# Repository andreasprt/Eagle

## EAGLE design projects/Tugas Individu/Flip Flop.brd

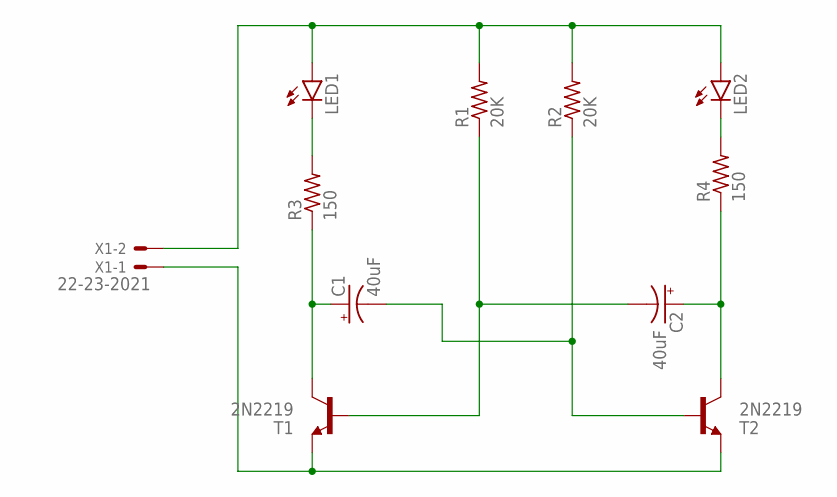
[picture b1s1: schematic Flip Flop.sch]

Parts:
C1, C2: 40uF; E2,5-6
LED1, LED2: LED5MM
R1, R2: 20K; 0207/10
R3, R4: 150; 0207/10
T1, T2: 2N2219; TO5
X1: 22-23-2021

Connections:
GND: T1.1 (E), T2.1 (E), X1.1
unnamed: LED1.K (C), R3.2
unnamed: LED2.K (C), R4.2
unnamed: C1.+, R3.1, T1.3 (C)
unnamed: C2.+, R4.1, T2.3 (C)
unnamed: C2.-, R1.1, T1.2 (B)
unnamed: C1.-, R2.1, T2.2 (B)
unnamed: LED1.A, LED2.A, R1.2, R2.2, X1.2

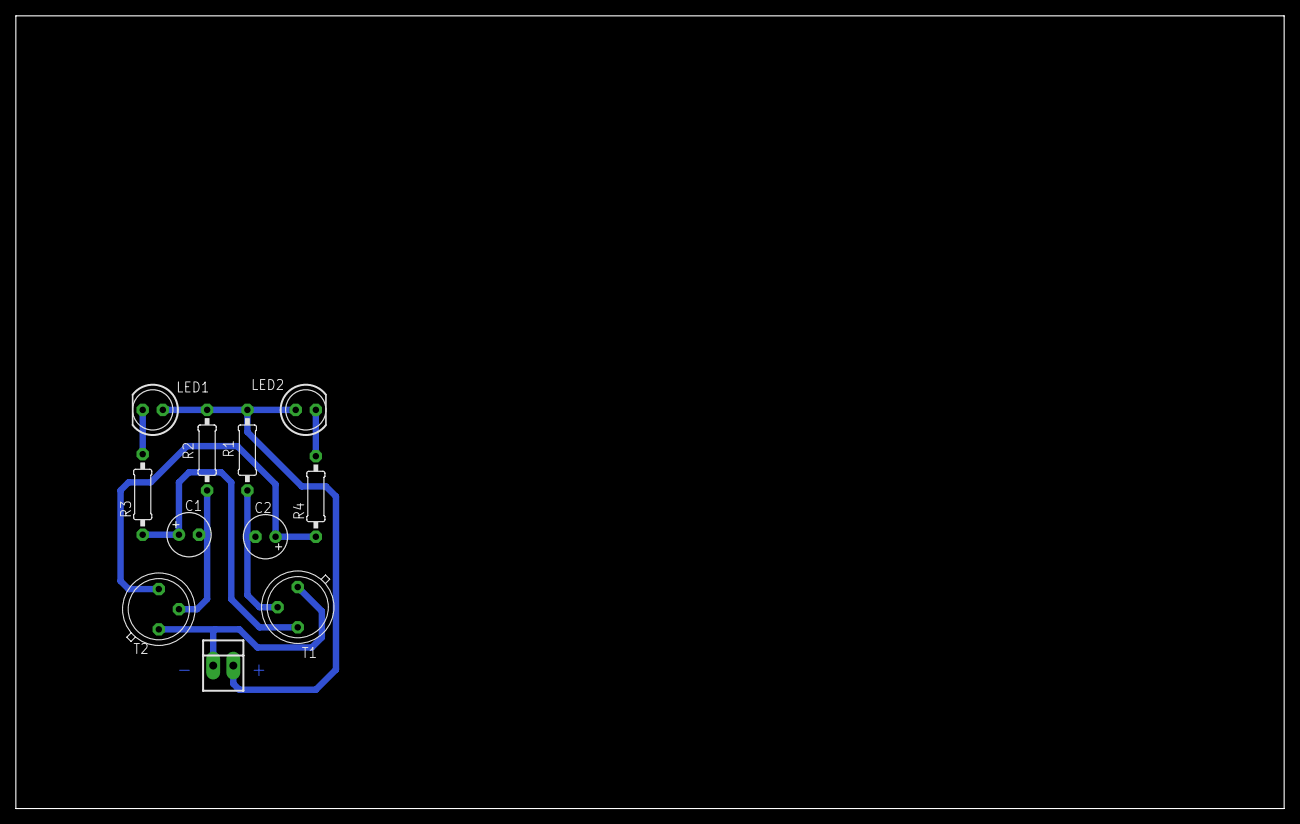
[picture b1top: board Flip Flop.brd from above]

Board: 2 copper layers, 160.0 x 100.0 mm, 11 parts (0 on the bottom side), 8 nets.

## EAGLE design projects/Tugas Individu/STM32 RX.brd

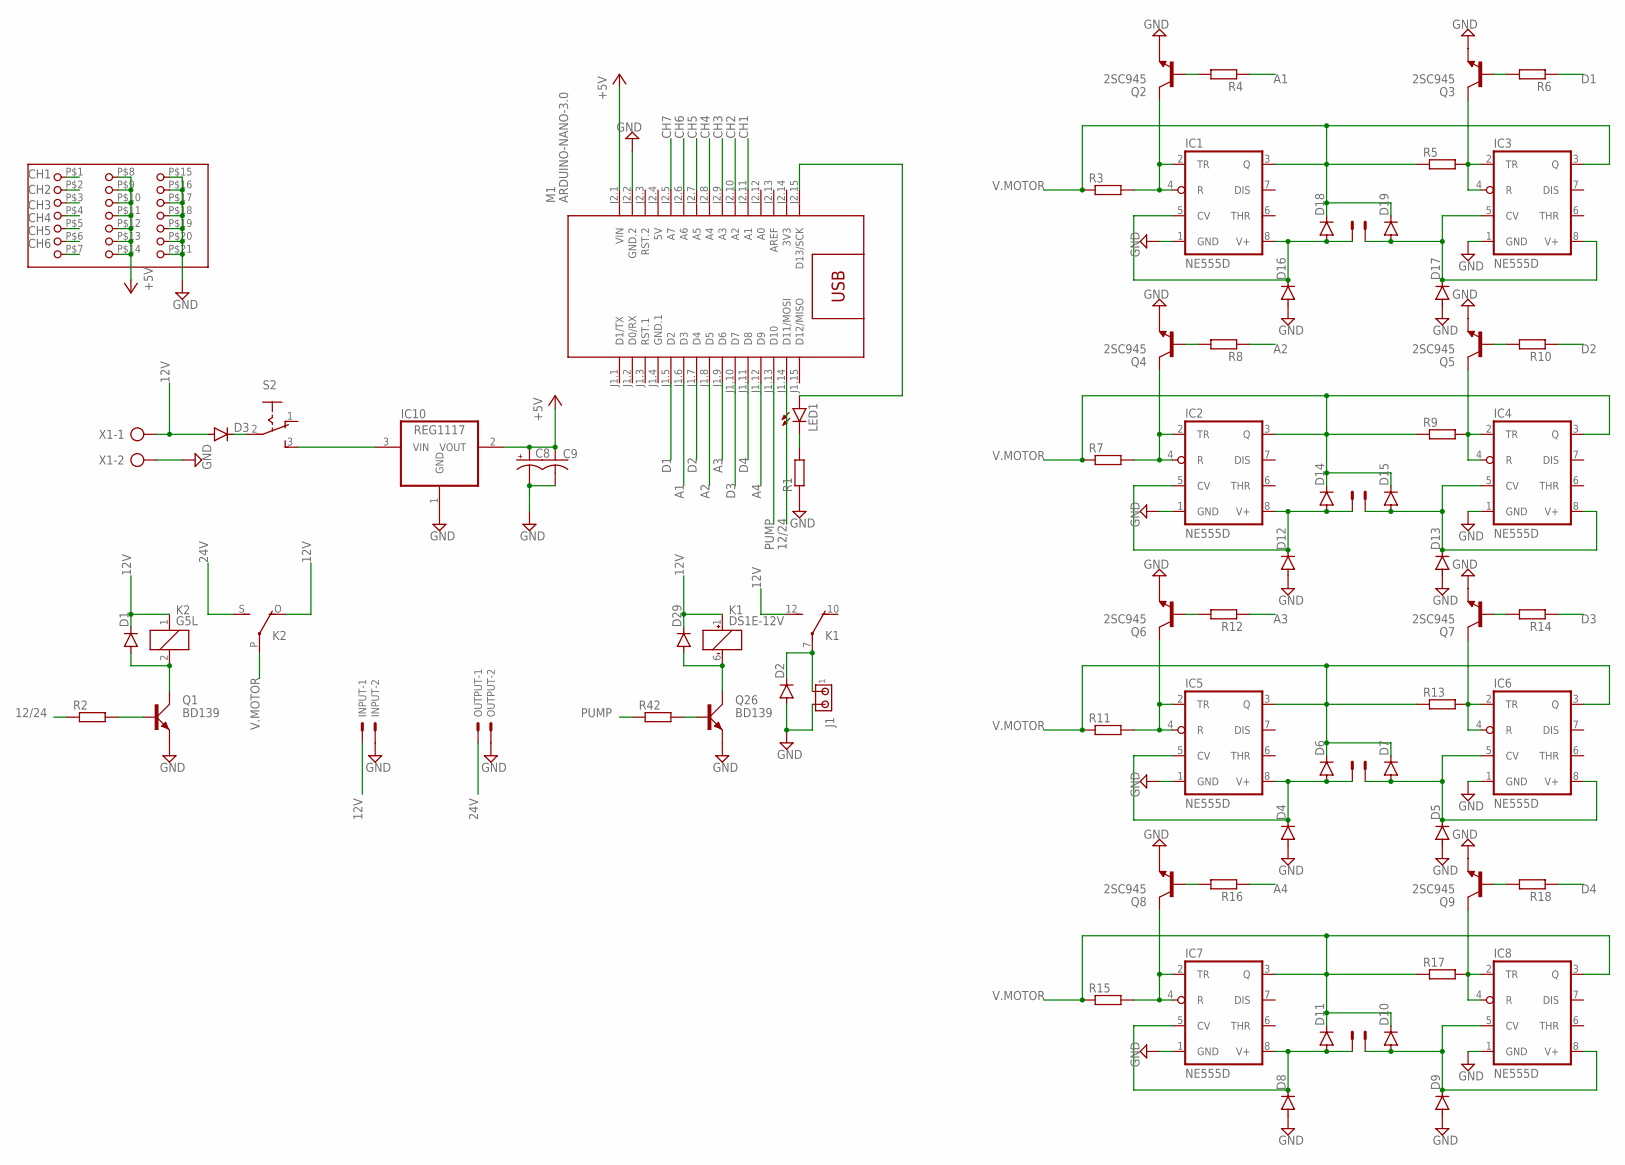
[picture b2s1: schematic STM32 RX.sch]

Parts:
C8: CPOL-USE2.5-6; E2,5-6
C9: C-US050-025X075; C050-025X075
D1, D2, D3, D4, D5, D6, D7, D8, D9, D10, D11, D12, D13, D14, D15, D16, D17, D18, D19, D29: 1N4933; DO41-10
IC1, IC2, IC3, IC4, IC5, IC6, IC7, IC8: NE555D; SO08
IC10: REG1117; SOT223
INPUT: 22-23-2021
J1: MTA02-156; 1X2MTA
K1: DS1E-12V; DS1E
K2: G5L; G5LE
LED1: LED5MM
M1: ARDUINO-NANO-3.0
OUTPUT, OUTPUT1, OUTPUT2, OUTPUT3, OUTPUT4: 22-23-2021
Q1, Q26: BD139; TO126AV
Q2, Q3, Q4, Q5, Q6, Q7, Q8, Q9: 2SC945; TO92-ECB
R1, R2, R3, R4, R5, R6, R7, R8, R9, R10, R11, R12, R13, R14, R15, R16, R17, R18, R42: R-EU_0207/10; 0207/10
S2: 255SB
U$1: PINHEAD3
X1: AK500/2

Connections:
3V3: M1.J2.14 (3V3)
5V: M1.J2.4 (5V)
12/24: M1.J1.14 (D11/MOSI), R2.1
12V: D1.C, D3.A, D29.C, INPUT.1, K1.1 (+), K1.12 (S), K2.1, K2.O, X1.1
24V: K2.S, OUTPUT.1
+5V: C8.+, C9.1, IC10.2 (VOUT), M1.J2.1 (VIN), U$1.P$8, U$1.P$9, U$1.P$10, U$1.P$11, U$1.P$12, U$1.P$13, U$1.P$14
A1: M1.J1.6 (D3), R4.1
A2: M1.J1.8 (D5), R8.1
A3: M1.J1.9 (D6), R12.1
A4: M1.J1.12 (D9), R16.1
CH1: M1.J2.11 (A1), U$1.P$1
CH2: M1.J2.10 (A2), U$1.P$2
CH3: M1.J2.9 (A3), U$1.P$3
CH4: M1.J2.8 (A4), U$1.P$4
CH5: M1.J2.7 (A5), U$1.P$5
CH6: M1.J2.6 (A6), U$1.P$6
CH7: M1.J2.5 (A7)
D1: M1.J1.5 (D2), R6.1
D2: M1.J1.7 (D4), R10.1
D3: M1.J1.10 (D7), R14.1
D4: M1.J1.11 (D8), R18.1
GND: C8.-, C9.2, D2.A, D4.A, D5.A, D8.A, D9.A, D12.A, D13.A, D16.A, D17.A, IC1.1 (GND), IC2.1 (GND), IC3.1 (GND), IC4.1 (GND), IC5.1 (GND), IC6.1 (GND), IC7.1 (GND), IC8.1 (GND), IC10.1 (GND), INPUT.2, J1.2, M1.J2.2 (GND.2), OUTPUT.2, Q1.E, Q2.E, Q3.E, Q4.E, Q5.E, Q6.E, Q7.E, Q8.E, Q9.E, Q26.E, R1.1, U$1.P$15, U$1.P$16, U$1.P$17, U$1.P$18, U$1.P$19, U$1.P$20, U$1.P$21, X1.2
GND.1: M1.J1.4 (GND.1)
unnamed: LED1.A, M1.J2.15 (D13/SCK)
unnamed: D1.A, K2.2, Q1.C
unnamed: LED1.K (C), R1.2
unnamed: Q1.B, R2.2
unnamed: D3.C, S2.2
unnamed: IC10.3 (VIN), S2.3 (S)
unnamed: IC1.2 (TR), IC1.4 (R), Q2.C, R3.2
unnamed: D16.C, D18.A, IC1.5 (CV), IC1.8 (V+), OUTPUT1.1
unnamed: IC2.2 (TR), IC2.4 (R), Q4.C, R7.2
unnamed: Q2.B, R4.2
unnamed: IC3.2 (TR), IC3.4 (R), Q3.C, R5.2
unnamed: D17.C, D19.A, IC3.5 (CV), IC3.8 (V+), OUTPUT1.2
unnamed: Q3.B, R6.2
unnamed: D12.C, D14.A, IC2.5 (CV), IC2.8 (V+), OUTPUT2.1
unnamed: Q4.B, R8.2
unnamed: IC4.2 (TR), IC4.4 (R), Q5.C, R9.2
unnamed: D13.C, D15.A, IC4.5 (CV), IC4.8 (V+), OUTPUT2.2
unnamed: Q5.B, R10.2
unnamed: IC5.2 (TR), IC5.4 (R), Q6.C, R11.2
unnamed: D4.C, D6.A, IC5.5 (CV), IC5.8 (V+), OUTPUT3.1
unnamed: Q6.B, R12.2
unnamed: IC6.2 (TR), IC6.4 (R), Q7.C, R13.2
unnamed: D5.C, D7.A, IC6.5 (CV), IC6.8 (V+), OUTPUT3.2
unnamed: Q7.B, R14.2
unnamed: IC7.2 (TR), IC7.4 (R), Q8.C, R15.2
unnamed: D8.C, D11.A, IC7.5 (CV), IC7.8 (V+), OUTPUT4.1
unnamed: Q8.B, R16.2
unnamed: IC8.2 (TR), IC8.4 (R), Q9.C, R17.2
unnamed: D9.C, D10.A, IC8.5 (CV), IC8.8 (V+), OUTPUT4.2
unnamed: Q9.B, R18.2
unnamed: D2.C, J1.1, K1.7
unnamed: D29.A, K1.6 (-), Q26.C
unnamed: Q26.B, R42.2
PUMP: M1.J1.13 (D10), R42.1
V.MOTOR: D6.C, D7.C, D10.C, D11.C, D14.C, D15.C, D18.C, D19.C, IC1.3 (Q), IC2.3 (Q), IC3.3 (Q), IC4.3 (Q), IC5.3 (Q), IC6.3 (Q), IC7.3 (Q), IC8.3 (Q), K2.P, R3.1, R5.1, R7.1, R9.1, R11.1, R13.1, R15.1, R17.1

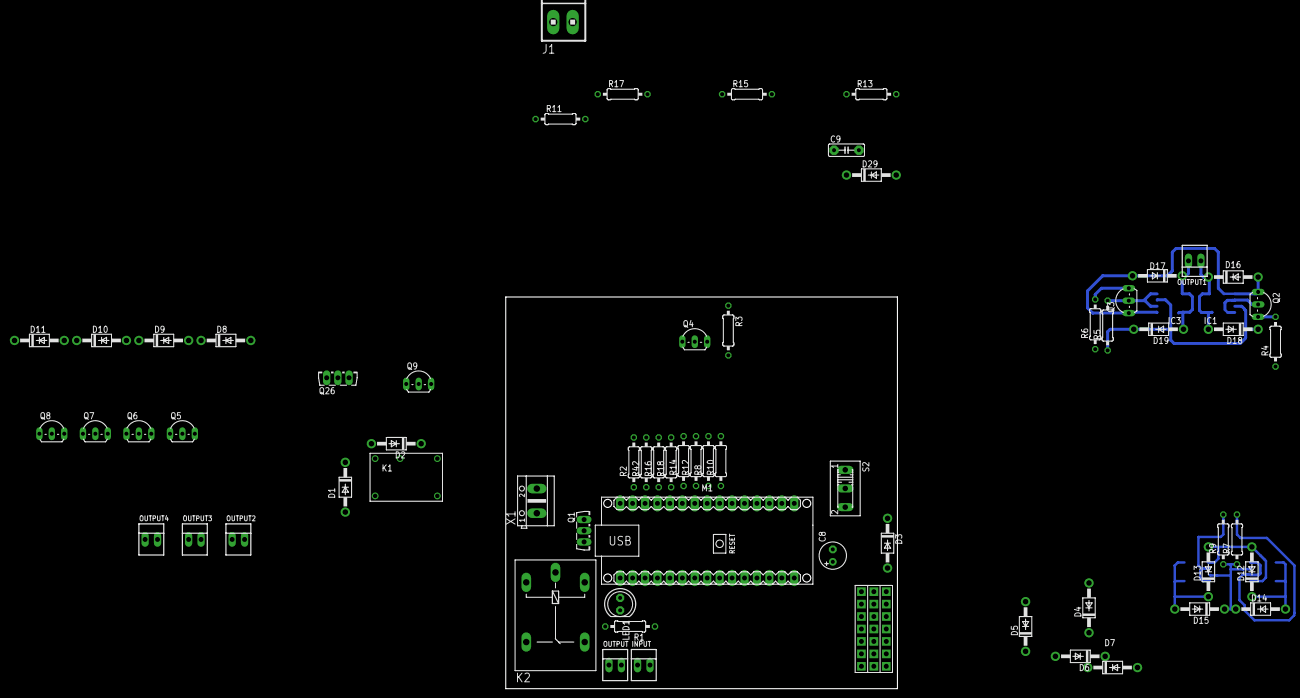
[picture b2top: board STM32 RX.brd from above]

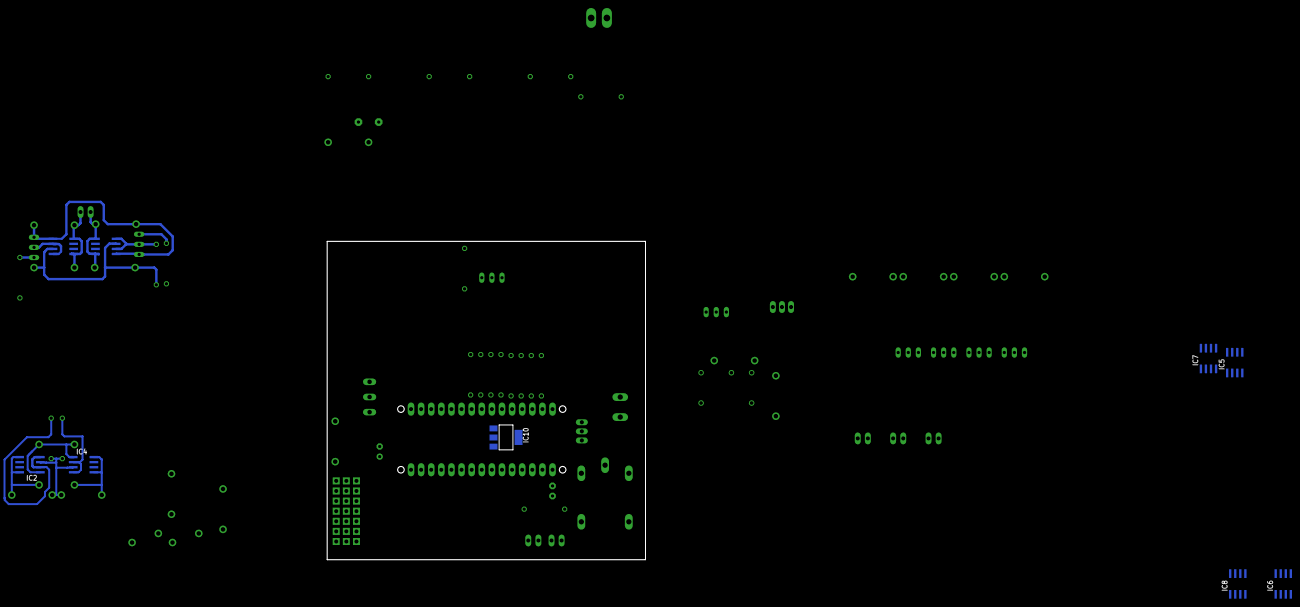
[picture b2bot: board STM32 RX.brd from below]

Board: 2 copper layers, 80.0 x 80.0 mm, 74 parts (9 on the bottom side), 54 nets.

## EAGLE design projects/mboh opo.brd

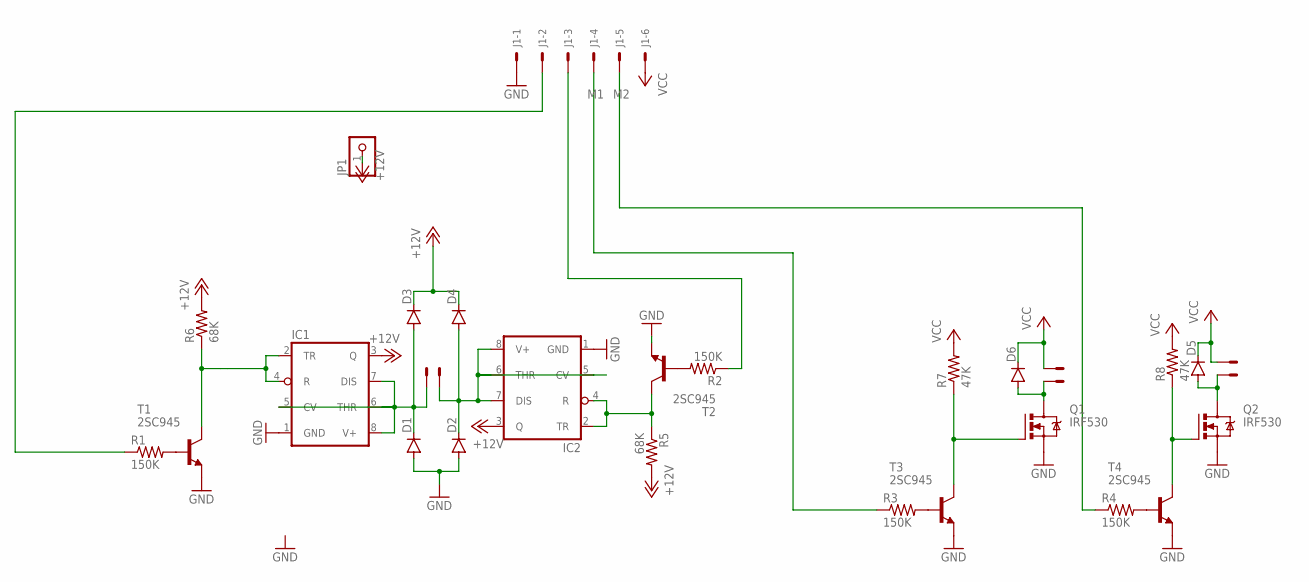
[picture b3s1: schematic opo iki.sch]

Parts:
D1, D2, D3, D4, D5, D6: 1N4004; DO41-10
IC1, IC2: LM555D; SO08
J1: 22-27-2061-06; 6410-06
JP1: PINHD-1X1; 1X01
Q1, Q2: IRF530; TO220BV
R1, R2, R3, R4: 150K; 0309/10
R5, R6: 68K; 0309/10
R7, R8: 47K; 0309/10
T1, T2, T3, T4: 2SC945; TO92-ECB
X1, X2, X3: 22-23-2021

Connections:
+12V: D3.C, D4.C, IC1.3 (Q), IC2.3 (Q), JP1.1, R5.2, R6.2
GND: D1.A, D2.A, IC1.1 (GND), IC2.1 (GND), J1.1, Q1.S, Q2.S, T1.E, T2.E, T3.E, T4.E
M1: J1.4, R3.1
M2: J1.5, R4.1
unnamed: R1.2, T1.B
unnamed: R2.2, T2.B
unnamed: IC2.2 (TR), IC2.4 (R), R5.1, T2.C
unnamed: IC1.2 (TR), IC1.4 (R), R6.1, T1.C
unnamed: R3.2, T3.B
unnamed: D1.C, D3.A, IC1.5 (CV), IC1.6 (THR), IC1.7 (DIS), IC1.8 (V+), X3.1
unnamed: D2.C, D4.A, IC2.5 (CV), IC2.6 (THR), IC2.7 (DIS), IC2.8 (V+), X3.2
unnamed: R4.2, T4.B
unnamed: Q1.G, R7.1, T3.C
unnamed: Q2.G, R8.1, T4.C
unnamed: D6.A, Q1.D, X1.2
unnamed: D5.A, Q2.D, X2.2
unnamed: J1.2, R1.1
unnamed: J1.3, R2.1
VCC: D5.C, D6.C, J1.6, R7.2, R8.2, X1.1, X2.1

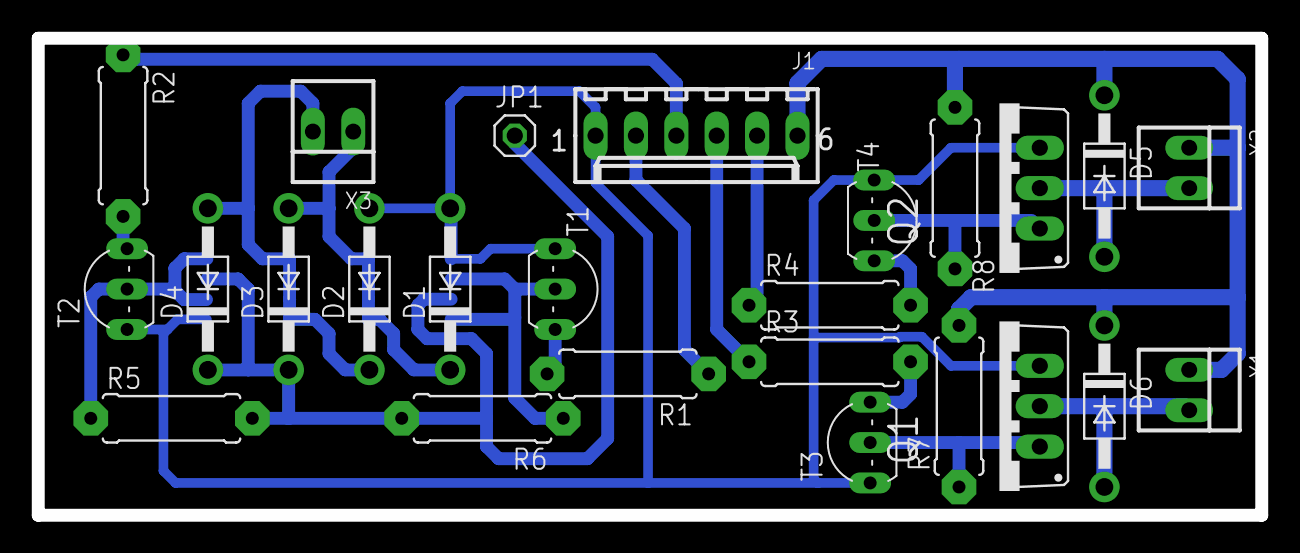
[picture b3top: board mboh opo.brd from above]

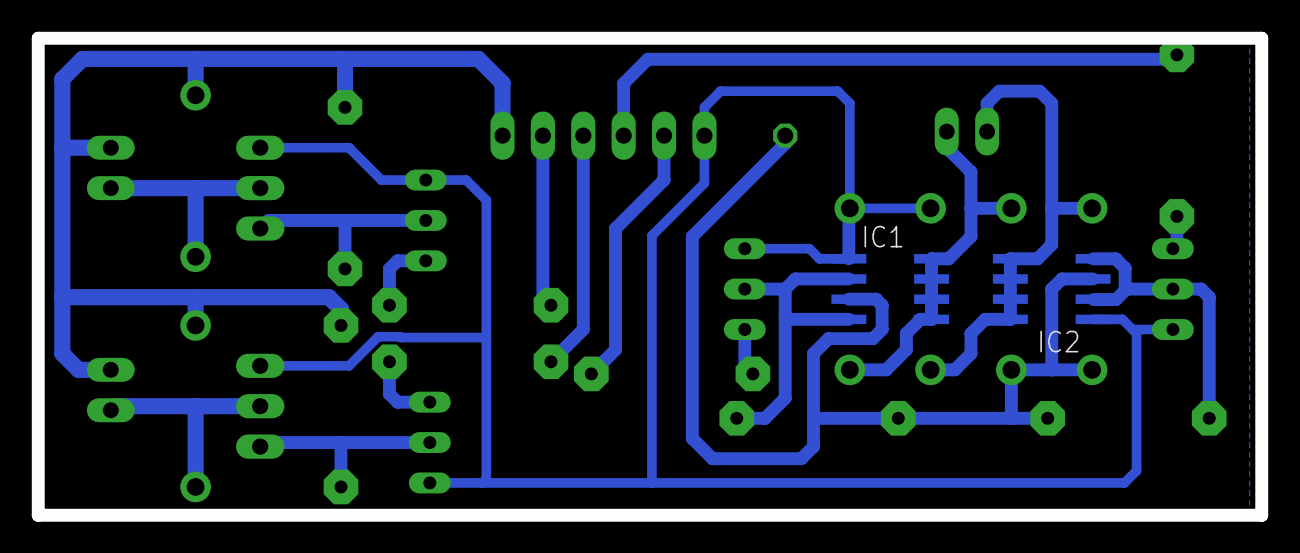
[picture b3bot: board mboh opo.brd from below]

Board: 2 copper layers, 77.0 x 30.0 mm, 27 parts (2 on the bottom side), 19 nets.

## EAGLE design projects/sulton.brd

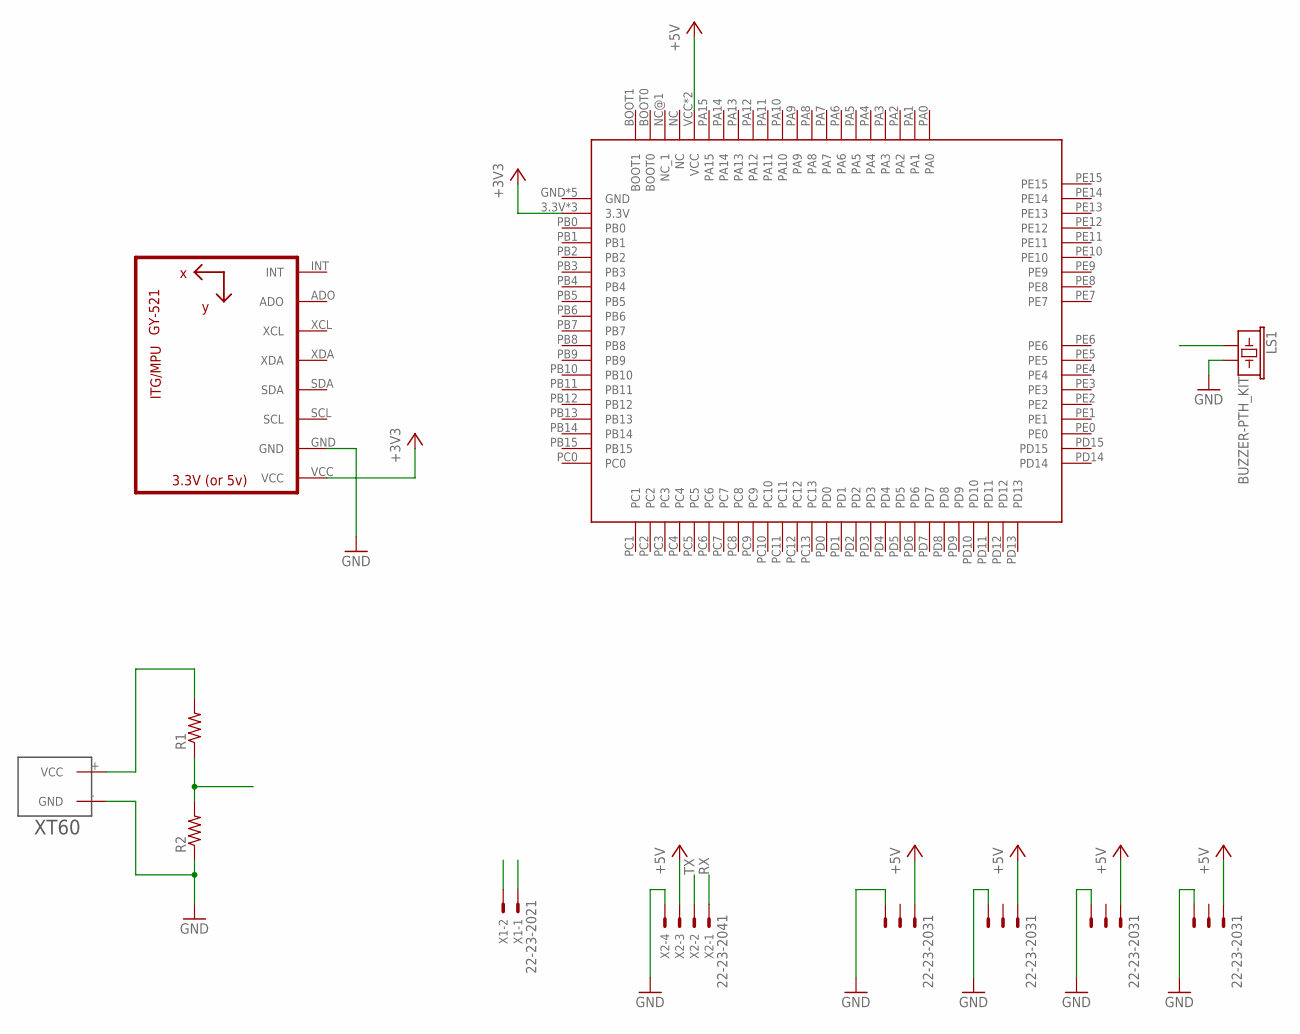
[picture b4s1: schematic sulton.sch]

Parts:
ESC1, ESC2, ESC3, ESC4: 22-23-2031
LS1: BUZZER-PTH_KIT; BUZZER-12MM-KIT
R1, R2: R-US_0207/10; 0207/10
U1: GY-521MPU6050; GY-521
U$1: STM32F4
U$2: XT60
X1: 22-23-2021
X2: 22-23-2041

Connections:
+3V3: U1.VCC, U$1.3.3V, U$1.3.3V@2 (3.3V), U$1.3.3V@3 (3.3V)
+5V: ESC1.1, ESC2.1, ESC3.1, ESC4.1, U$1.VCC, U$1.VCC@1 (VCC), X2.3
GND: ESC1.3, ESC2.3, ESC3.3, ESC4.3, LS1.- (2), R2.1, U1.GND, U$2.- (GND), X2.4
unnamed: R1.2, U$2.+ (VCC)
unnamed: R1.1, R2.2
RX: X2.1
TX: X2.2

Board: 2 copper layers, 12 parts (0 on the bottom side), 5 nets, no tracks yet.

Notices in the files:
parts and their libraries:
diy-modules: Released under the Creative Commons Attribution 4.0 International License: http://creativecommons.org/licenses/by/4.0
SparkFun-Electromechanical: Licensing: Creative Commons ShareAlike 4.0 International - https://creativecommons.org/licenses/by-sa/4.0
